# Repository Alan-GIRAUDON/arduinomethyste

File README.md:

# Arduinomethyste

## Summary of the project

Arduinomethyste is a printed circuit board (PCB) based on the ATMega328PB from Atmel. It is the more recent version of the ATMega328P used in the Arduino Uno. The goal of this project is to design a minimalist but functional board compatible with the Arduino framework.

## Schematics

## Features

- USB-C with USB-UART converter (CH340N) for the serial communication Computer-ATMega328PB
- BOOT button to configure the firmware and RESET the board
- Power red LED indicating a proper 5V rail (USB or pins)
- Green LED linked to a PWM of the ATMega328PB to control its light intensity
- Expose every pins except PD5 (used by the green LED) and the RESET (a mistake to correct)
- Expose power pins (5V and GND)

## Components and making

The board was conceived to be assembled by JLCPCB, the components references are theirs and the constraints of the Kicad projects are adapted to JLCPCB limitations.

Fortunately, the board doesn't require controled impedance (the USB trace are very short), the sizes and spacing (traces and vias) being generous, it is totally feasible to make this board with other fabricators (Aisler, OshPark, PCBWay). The components references just need to be adjusted accordingly (be aware of footprints variation) to the fabricator or the distributor (Mouser, Digikey), if you assemble the board yourself.

## Board results :

## Firmware and Arduino programming
By default, the ATMega328PB chips don't the contain the firmware required for the Arduino framework, it is necessary to use the ICSP protocol to upload it.

The easiest way is the use an Arduino Uno (or nano) as a programmer to upload the firmware. For that, we link the ICSP pins of the boards and use the Arduino IDE to upload the code.

The ATMega328PB possess its own firmware with a few additional features but for compatibility reasons, it is simpler to use the original ATMega328P firmware.

## Current Issues and TO DO list

- The current version doesn't use an external crystal to remain as minimalist as possible, the issue being that it seems necessary for the serial converter communication, as of today only the ICSP protocol as be shown to be working
- The RESET pin is needed for the ICSP protocol but it isn't exposed which complicate firmware flashing

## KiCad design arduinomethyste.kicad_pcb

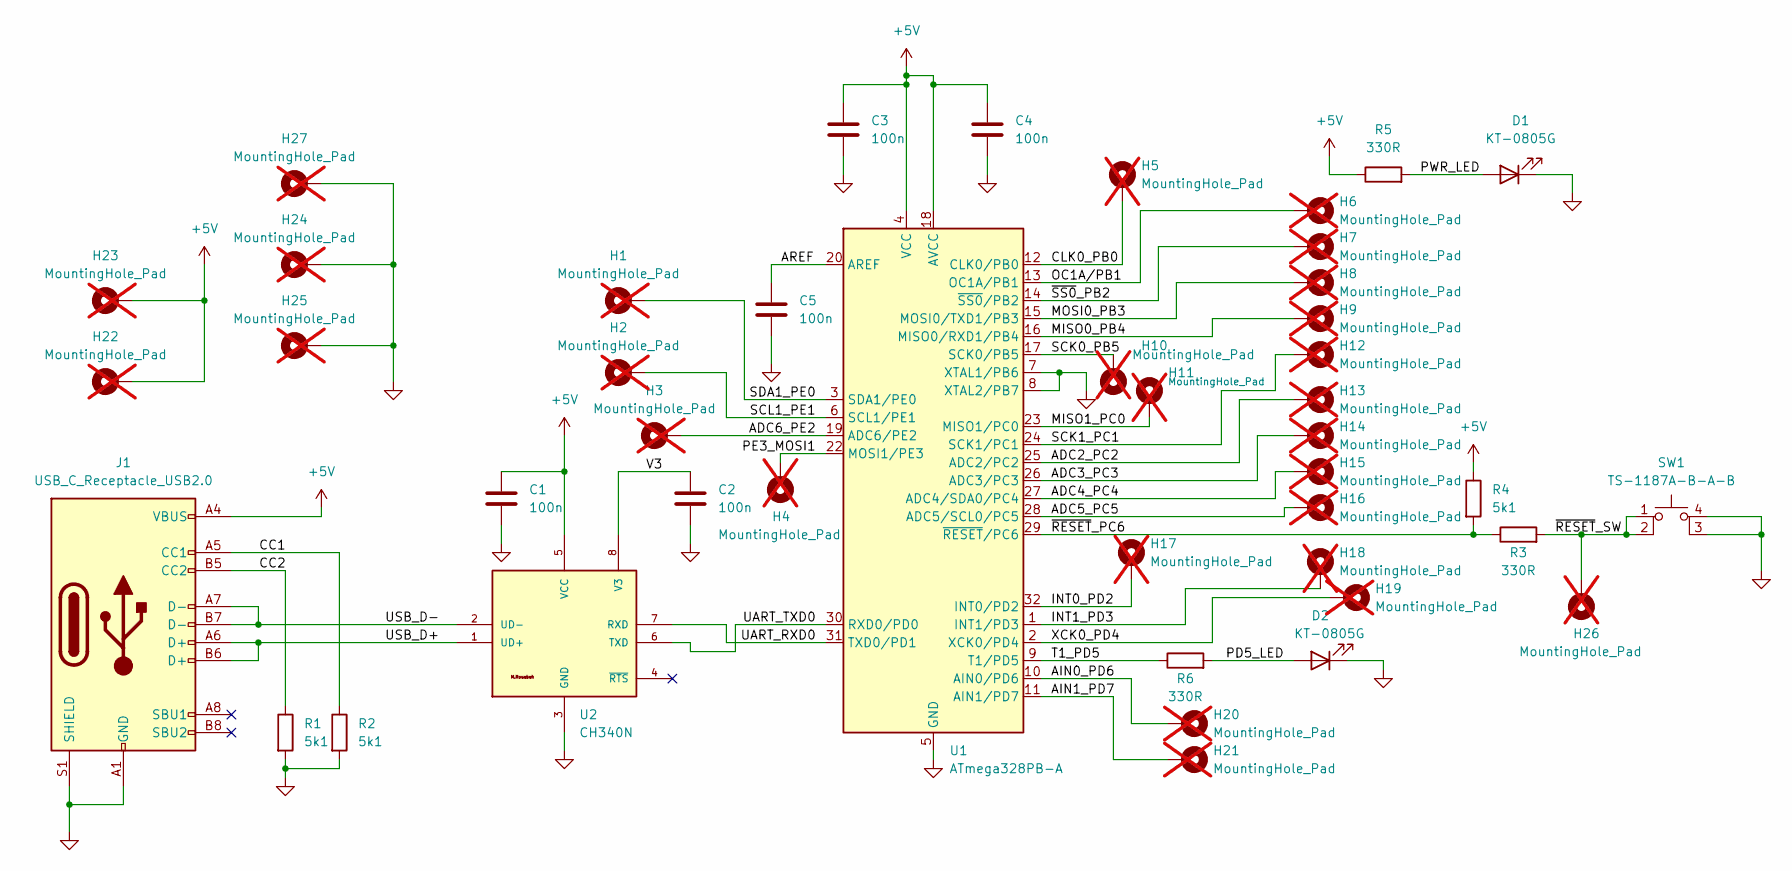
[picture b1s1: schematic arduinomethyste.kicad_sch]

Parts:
C1, C2, C3, C4, C5: 100n; C_0402_1005Metric; JLCPCB Position Offset 0,0
D1, D2: KT-0805G; C_0805_2012Metric; JLCPCB Position Offset 0,0
H1, H2, H3, H4, H5, H6, H7, H8, H9, H10, H11, H12, H13, H14, H15, H16, H17, H18, H19, H20, H21, H22, H23, H24, H25, H26, H27: MountingHole_Pad; Pin_D0.7mm_L6.5mm_W1.8mm_FlatFork; JLCPCB Position Offset 0,0; not fitted
J1: USB_C_Receptacle_USB2.0; USB_C_Receptacle_G-Switch_GT-USB-7010ASV; JLCPCB Position Offset 0,1.2
R1, R2, R4: 5k1; R_0402_1005Metric; JLCPCB Position Offset 0,0
R3, R5, R6: 330R; R_0402_1005Metric; JLCPCB Position Offset 0,0
SW1: TS-1187A-B-A-B; SW_Push_1P1T_XKB_TS-1187A; JLCPCB Position Offset 0,0
U1: ATmega328PB-A; TQFP-32_7x7mm_P0.8mm; JLCPCB Position Offset 0,0
U2: CH340N; JLCPCB Position Offset 0,0

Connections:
+5V: C1.1, C3.2, C4.1, H22.1, H23.1, J1.A4 (VBUS), J1.A9 (VBUS), J1.B4 (VBUS), J1.B9 (VBUS), R4.1, R5.1, U1.4 (VCC), U1.18 (AVCC), U2.5 (VCC)
/ADC2_PC2: H13.1, U1.25 (ADC2/PC2)
/ADC3_PC3: H14.1, U1.26 (ADC3/PC3)
/ADC4_PC4: H15.1, U1.27 (ADC4/SDA0/PC4)
/ADC5_PC5: H16.1, U1.28 (ADC5/SCL0/PC5)
/ADC6_PE2: H3.1, U1.19 (ADC6/PE2)
/AIN0_PD6: H20.1, U1.10 (AIN0/PD6)
/AIN1_PD7: H21.1, U1.11 (AIN1/PD7)
/AREF: C5.1, U1.20 (AREF)
/CC1: J1.A5 (CC1), R2.1
/CC2: J1.B5 (CC2), R1.1
/CLK0_PB0: H5.1, U1.12 (CLK0/PB0)
/INT0_PD2: H17.1, U1.32 (INT0/PD2)
/INT1_PD3: H18.1, U1.1 (INT1/PD3)
/MISO0_PB4: H9.1, U1.16 (MISO0/RXD1/PB4)
/MISO1_PC0: H11.1, U1.23 (MISO1/PC0)
/MOSI0_PB3: H8.1, U1.15 (MOSI0/TXD1/PB3)
/OC1A/PB1: H6.1, U1.13 (OC1A/PB1)
/PD5_LED: D2.2 (A), R6.2
/PE3_MOSI1: H4.1, U1.22 (MOSI1/PE3)
/PWR_LED: D1.2 (A), R5.2
/SCK0_PB5: H10.1, U1.17 (SCK0/PB5)
/SCK1_PC1: H12.1, U1.24 (SCK1/PC1)
/SCL1_PE1: H2.1, U1.6 (SCL1/PE1)
/SDA1_PE0: H1.1, U1.3 (SDA1/PE0)
/T1_PD5: R6.1, U1.9 (T1/PD5)
/UART_RXD0: U1.31 (TXD0/PD1), U2.7 (RXD)
/UART_TXD0: U1.30 (RXD0/PD0), U2.6 (TXD)
/USB_D+: J1.A6 (D+), J1.B6 (D+), U2.1 (UD+)
/USB_D-: J1.A7 (D-), J1.B7 (D-), U2.2 (UD-)
/V3: C2.1, U2.8 (V3)
/XCK0_PD4: H19.1, U1.2 (XCK0/PD4)
/~RESET_PC6: R3.1, R4.2, U1.29 (~RESET/PC6)
/~RESET_SW: H26.1, R3.2, SW1.1, SW1.2
/~SS0_PB2: H7.1, U1.14 (~SS0/PB2)
GND: C1.2, C2.2, C3.1, C4.2, C5.2, D1.1 (K), D2.1 (K), H24.1, H25.1, H27.1, J1.A1 (GND), J1.A12 (GND), J1.B1 (GND), J1.B12 (GND), J1.S1 (SHIELD), R1.2, R2.2, SW1.3 (K), SW1.4 (A), U1.5 (GND), U1.7 (XTAL1/PB6), U1.8 (XTAL2/PB7), U1.21 (GND), U2.3 (GND)

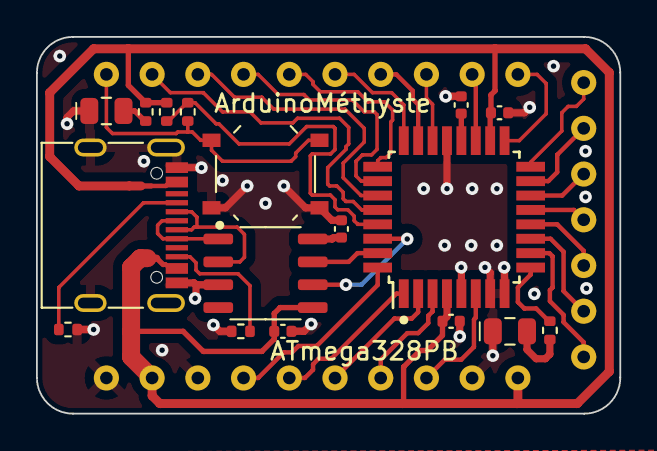
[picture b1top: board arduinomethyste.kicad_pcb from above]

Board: 2 copper layers, 32.4 x 20.9 mm, 44 parts (0 on the bottom side), 36 nets.

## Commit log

2024-11-30 readme test cube
2024-11-30 readme test pcb no silk, traces
2024-11-30 readme remove stl viewer
2024-12-04 Create LICENSE
